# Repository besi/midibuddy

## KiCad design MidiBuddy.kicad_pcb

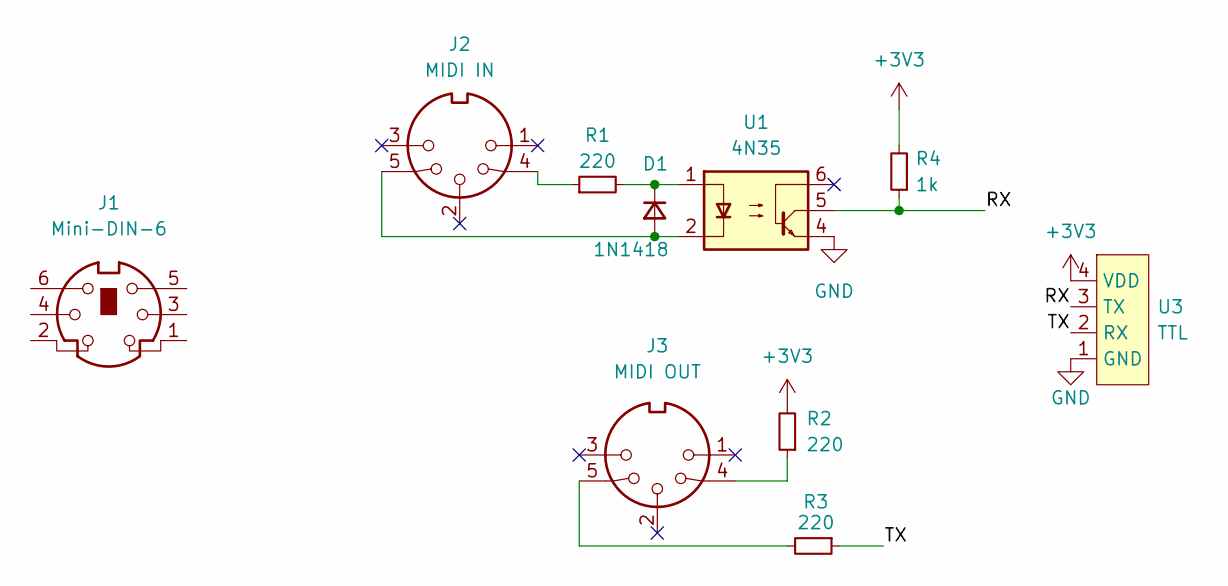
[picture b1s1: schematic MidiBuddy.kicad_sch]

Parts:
D1: 1N1418; D_A-405_P7.62mm_Horizontal
J1: Mini-DIN-6
J2: MIDI IN; midi
J3: MIDI OUT; midi
R1, R2, R3: 220; R_Axial_DIN0207_L6.3mm_D2.5mm_P7.62mm_Horizontal
R4: 1k; R_Axial_DIN0207_L6.3mm_D2.5mm_P7.62mm_Horizontal
U1: 4N35; DIP-6_W7.62mm
U3: TTL; PinHeader_1x04_P2.54mm_Vertical

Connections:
+3V3: R2.2, R4.2, U3.4 (VDD)
/RX: R4.1, U1.5, U3.3 (TX)
/TX: R3.1, U3.2 (RX)
GND: U1.4, U3.1 (GND)
unnamed: D1.1 (K), R1.2, U1.1
unnamed: D1.2 (A), J2.5, U1.2
unnamed: J2.4, R1.1
unnamed: J3.4, R2.1
unnamed: J3.5, R3.2

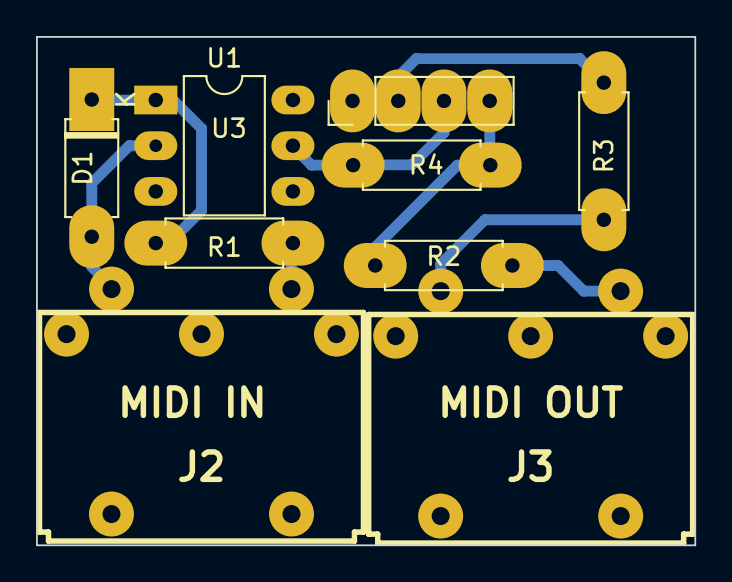
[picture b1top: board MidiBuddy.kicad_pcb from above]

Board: 2 copper layers, 36.6 x 28.2 mm, 9 parts (0 on the bottom side), 9 nets.

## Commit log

2023-05-09 Add midi socket
2023-05-12 Initial pcb design
2023-05-12 Minor adjustments
2023-05-12 Initial commit of the corresponding Micropython software
2025-04-01 Adapt for ESP32 S3
